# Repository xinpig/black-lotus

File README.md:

# black-lotus
Split ortholinear keyboard

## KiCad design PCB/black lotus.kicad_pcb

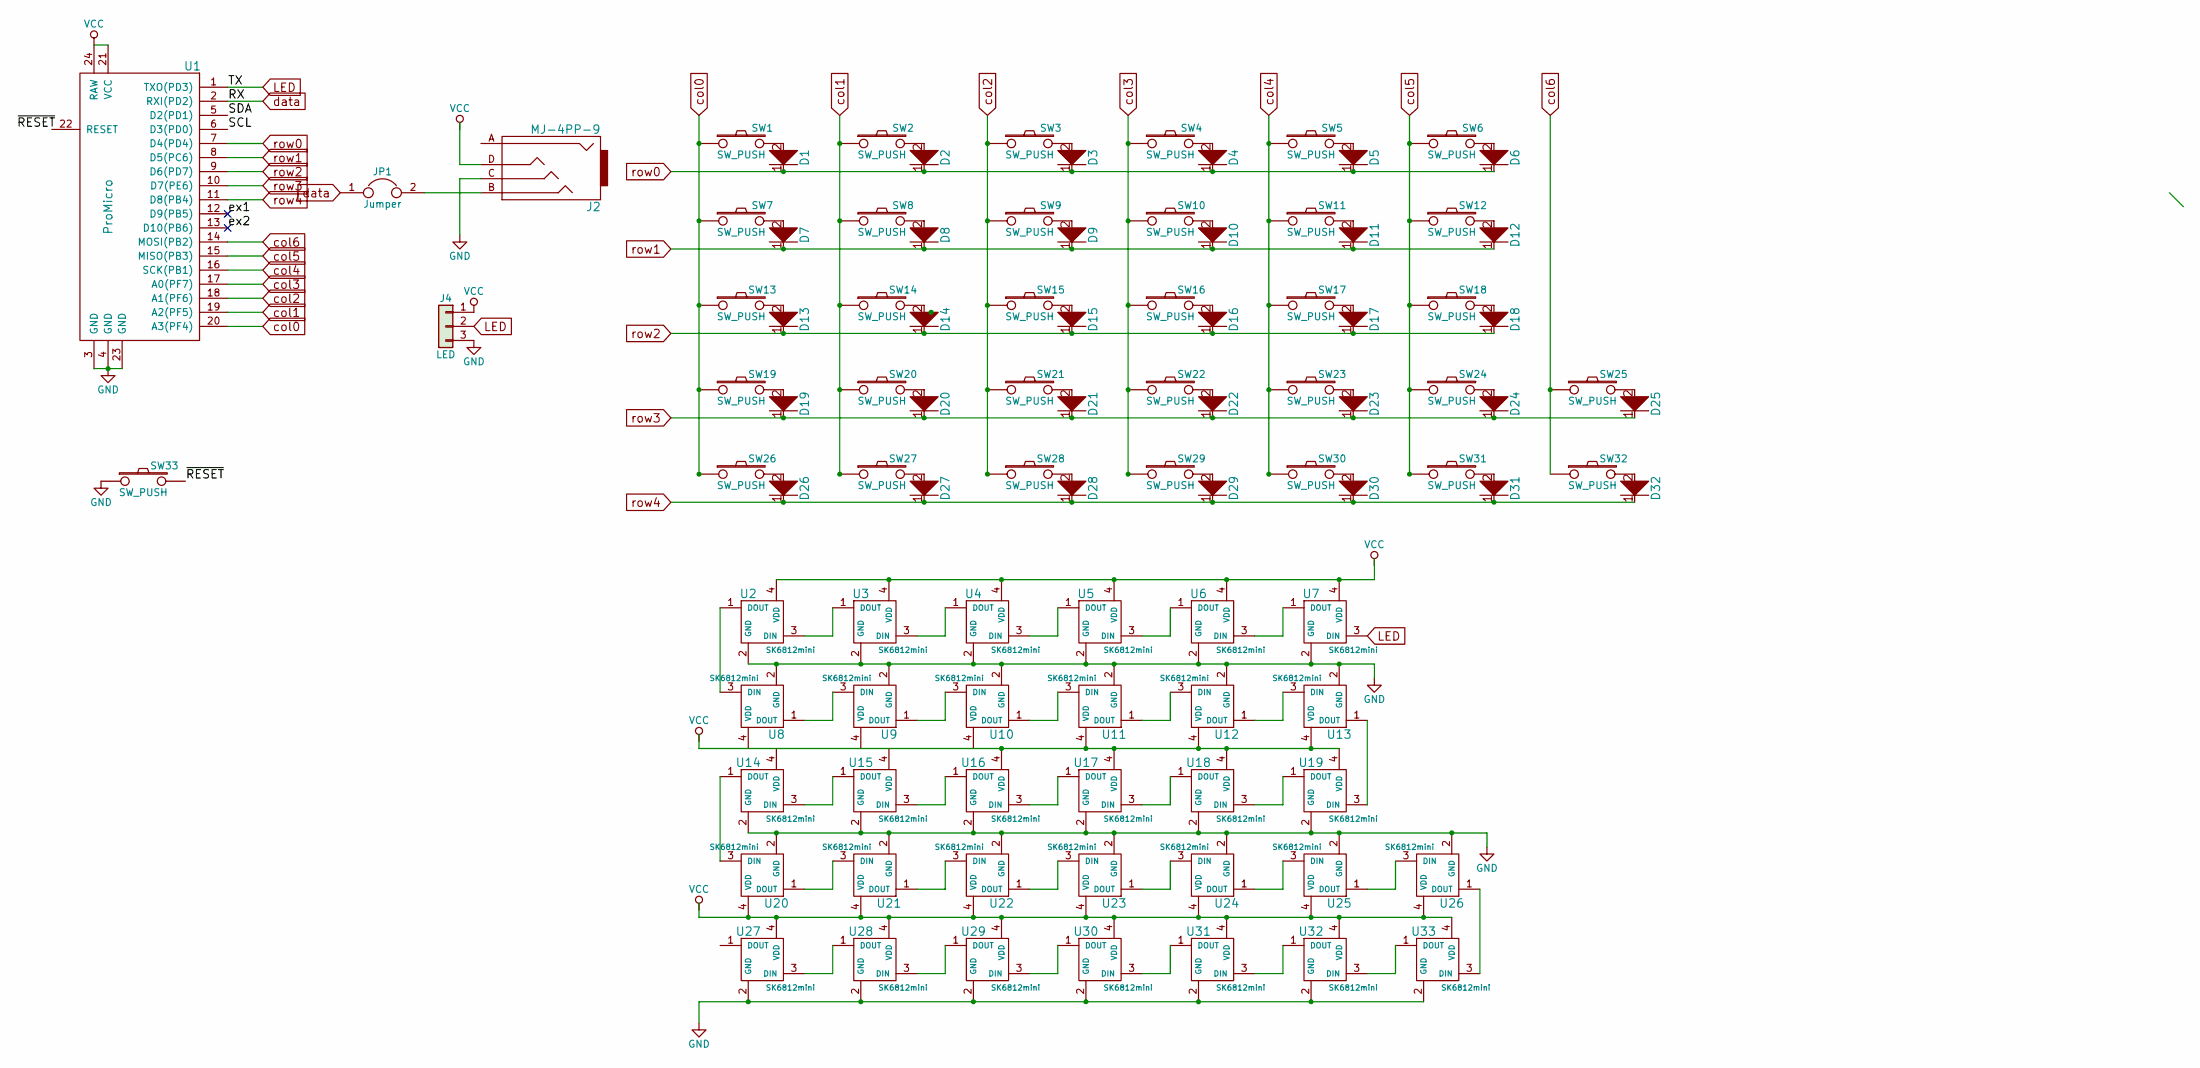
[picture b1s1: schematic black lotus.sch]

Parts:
D1, D2, D3, D4, D5, D6, D7, D8, D9, D10, D11, D12, D13, D14, D15, D16, D17, D18, D19, D20, D21, D22, D23, D24, D25, D26, D27, D28, D29, D30, D31, D32: D; D3_TH_SMD
J2: MJ-4PP-9; MJ-4PP-9_rev2
J4: LED; StripLED_rev
JP1: Jumper; JPC2
SW1, SW2, SW3, SW4, SW5, SW6, SW7, SW8, SW9, SW10, SW11, SW12, SW13, SW14, SW15, SW16, SW17, SW18, SW19, SW20, SW21, SW22, SW23, SW24, SW25, SW26, SW27, SW28, SW29, SW30, SW31, SW32: SW_PUSH; Kailh_MX_Socket_reversible
SW33: SW_PUSH; SW_3.5x6.0_TH
U1: ProMicro; ProMicro_rev
U2, U3, U4, U5, U6, U7, U8, U9, U10, U11, U12, U13, U14, U15, U16, U17, U18, U19, U20, U21, U22, U23, U24, U25, U26, U27, U28, U29, U30, U31, U32, U33: SK6812mini; SK6812MINI_rev

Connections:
/SCL: U1.6 (D3(PD0)); also elsewhere on the board
/SDA: U1.5 (D2(PD1)); also elsewhere on the board
/ex1: U1.12 (D9(PB5)); also elsewhere on the board
/ex2: U1.13 (D10(PB6)); also elsewhere on the board
/~RESET: SW33.2, U1.22 (RESET); also elsewhere on the board
GND: J2.C, J4.3, SW33.1, U1.3 (GND), U1.4 (GND), U1.23 (GND), U2.2 (GND), U3.2 (GND), U4.2 (GND), U5.2 (GND), U6.2 (GND), U7.2 (GND), U8.2 (GND), U9.2 (GND), U10.2 (GND), U11.2 (GND), U12.2 (GND), U13.2 (GND), U14.2 (GND), U15.2 (GND), U16.2 (GND), U17.2 (GND), U18.2 (GND), U19.2 (GND), U20.2 (GND), U21.2 (GND), U22.2 (GND), U23.2 (GND), U24.2 (GND), U25.2 (GND), U26.2 (GND), U27.2 (GND), U28.2 (GND), U29.2 (GND), U30.2 (GND), U31.2 (GND), U32.2 (GND), U33.2 (GND); also elsewhere on the board
LED: J4.2, U1.1 (TXO(PD3)), U7.3 (DIN); also elsewhere on the board
unnamed: D1.2, SW1.2
unnamed: D2.2, SW2.2
unnamed: D3.2, SW3.2
unnamed: D4.2, SW4.2
unnamed: D5.2, SW5.2
unnamed: D6.2, SW6.2
unnamed: D7.2, SW7.2
unnamed: D8.2, SW8.2
unnamed: D9.2, SW9.2
unnamed: D10.2, SW10.2
unnamed: D11.2, SW11.2
unnamed: D12.2, SW12.2
unnamed: D13.2, SW13.2
unnamed: D14.2, SW14.2
unnamed: D15.2, SW15.2
unnamed: D16.2, SW16.2
unnamed: D17.2, SW17.2
unnamed: D18.2, SW18.2
unnamed: D19.2, SW19.2
unnamed: D20.2, SW20.2
unnamed: D21.2, SW21.2
unnamed: D22.2, SW22.2
unnamed: D23.2, SW23.2
unnamed: D24.2, SW24.2
unnamed: D25.2, SW25.2
unnamed: D26.2, SW26.2
unnamed: D27.2, SW27.2
unnamed: D28.2, SW28.2
unnamed: D29.2, SW29.2
unnamed: D30.2, SW30.2
unnamed: D31.2, SW31.2
unnamed: D32.2, SW32.2
unnamed: J2.B, JP1.2
unnamed: U2.1 (DOUT), U8.3 (DIN)
unnamed: U2.3 (DIN), U3.1 (DOUT)
unnamed: U3.3 (DIN), U4.1 (DOUT)
unnamed: U4.3 (DIN), U5.1 (DOUT)
unnamed: U5.3 (DIN), U6.1 (DOUT)
unnamed: U6.3 (DIN), U7.1 (DOUT)
unnamed: U8.1 (DOUT), U9.3 (DIN)
unnamed: U10.1 (DOUT), U11.3 (DIN)
unnamed: U9.1 (DOUT), U10.3 (DIN)
unnamed: U11.1 (DOUT), U12.3 (DIN)
unnamed: U12.1 (DOUT), U13.3 (DIN)
unnamed: U13.1 (DOUT), U19.3 (DIN)
unnamed: U14.1 (DOUT), U20.3 (DIN)
unnamed: U14.3 (DIN), U15.1 (DOUT)
unnamed: U15.3 (DIN), U16.1 (DOUT)
unnamed: U16.3 (DIN), U17.1 (DOUT)
unnamed: U17.3 (DIN), U18.1 (DOUT)
unnamed: U18.3 (DIN), U19.1 (DOUT)
unnamed: U20.1 (DOUT), U21.3 (DIN)
unnamed: U21.1 (DOUT), U22.3 (DIN)
unnamed: U22.1 (DOUT), U23.3 (DIN)
unnamed: U23.1 (DOUT), U24.3 (DIN)
unnamed: U24.1 (DOUT), U25.3 (DIN)
unnamed: U25.1 (DOUT), U26.3 (DIN)
unnamed: U26.1 (DOUT), U33.3 (DIN)
unnamed: U27.3 (DIN), U28.1 (DOUT)
unnamed: U28.3 (DIN), U29.1 (DOUT)
unnamed: U29.3 (DIN), U30.1 (DOUT)
unnamed: U30.3 (DIN), U31.1 (DOUT)
unnamed: U31.3 (DIN), U32.1 (DOUT)
unnamed: U32.3 (DIN), U33.1 (DOUT)
VCC: J2.D, J4.1, U1.21 (VCC), U1.24 (RAW), U2.4 (VDD), U3.4 (VDD), U4.4 (VDD), U5.4 (VDD), U6.4 (VDD), U7.4 (VDD), U8.4 (VDD), U9.4 (VDD), U10.4 (VDD), U11.4 (VDD), U12.4 (VDD), U13.4 (VDD), U14.4 (VDD), U15.4 (VDD), U16.4 (VDD), U17.4 (VDD), U18.4 (VDD), U19.4 (VDD), U20.4 (VDD), U21.4 (VDD), U22.4 (VDD), U23.4 (VDD), U24.4 (VDD), U25.4 (VDD), U26.4 (VDD), U27.4 (VDD), U28.4 (VDD), U29.4 (VDD), U30.4 (VDD), U31.4 (VDD), U32.4 (VDD), U33.4 (VDD); also elsewhere on the board
col0: SW1.1, SW7.1, SW13.1, SW19.1, SW26.1, U1.20 (A3(PF4)); also elsewhere on the board
col1: SW2.1, SW8.1, SW14.1, SW20.1, SW27.1, U1.19 (A2(PF5)); also elsewhere on the board
col2: SW3.1, SW9.1, SW15.1, SW21.1, SW28.1, U1.18 (A1(PF6)); also elsewhere on the board
col3: SW4.1, SW10.1, SW16.1, SW22.1, SW29.1, U1.17 (A0(PF7)); also elsewhere on the board
col4: SW5.1, SW11.1, SW17.1, SW23.1, SW30.1, U1.16 (SCK(PB1)); also elsewhere on the board
col5: SW6.1, SW12.1, SW18.1, SW24.1, SW31.1, U1.15 (MISO(PB3)); also elsewhere on the board
col6: SW25.1, SW32.1, U1.14 (MOSI(PB2)); also elsewhere on the board
data: JP1.1, U1.2 (RXI(PD2)); also elsewhere on the board
row0: D1.1, D2.1, D3.1, D4.1, D5.1, D6.1, U1.7 (D4(PD4)); also elsewhere on the board
row1: D7.1, D8.1, D9.1, D10.1, D11.1, D12.1, U1.8 (D5(PC6)); also elsewhere on the board
row2: D13.1, D14.1, D15.1, D16.1, D17.1, D18.1, U1.9 (D6(PD7)); also elsewhere on the board
row3: D19.1, D20.1, D21.1, D22.1, D23.1, D24.1, D25.1, U1.10 (D7(PE6)); also elsewhere on the board
row4: D26.1, D27.1, D28.1, D29.1, D30.1, D31.1, D32.1, U1.11 (D8(PB4)); also elsewhere on the board

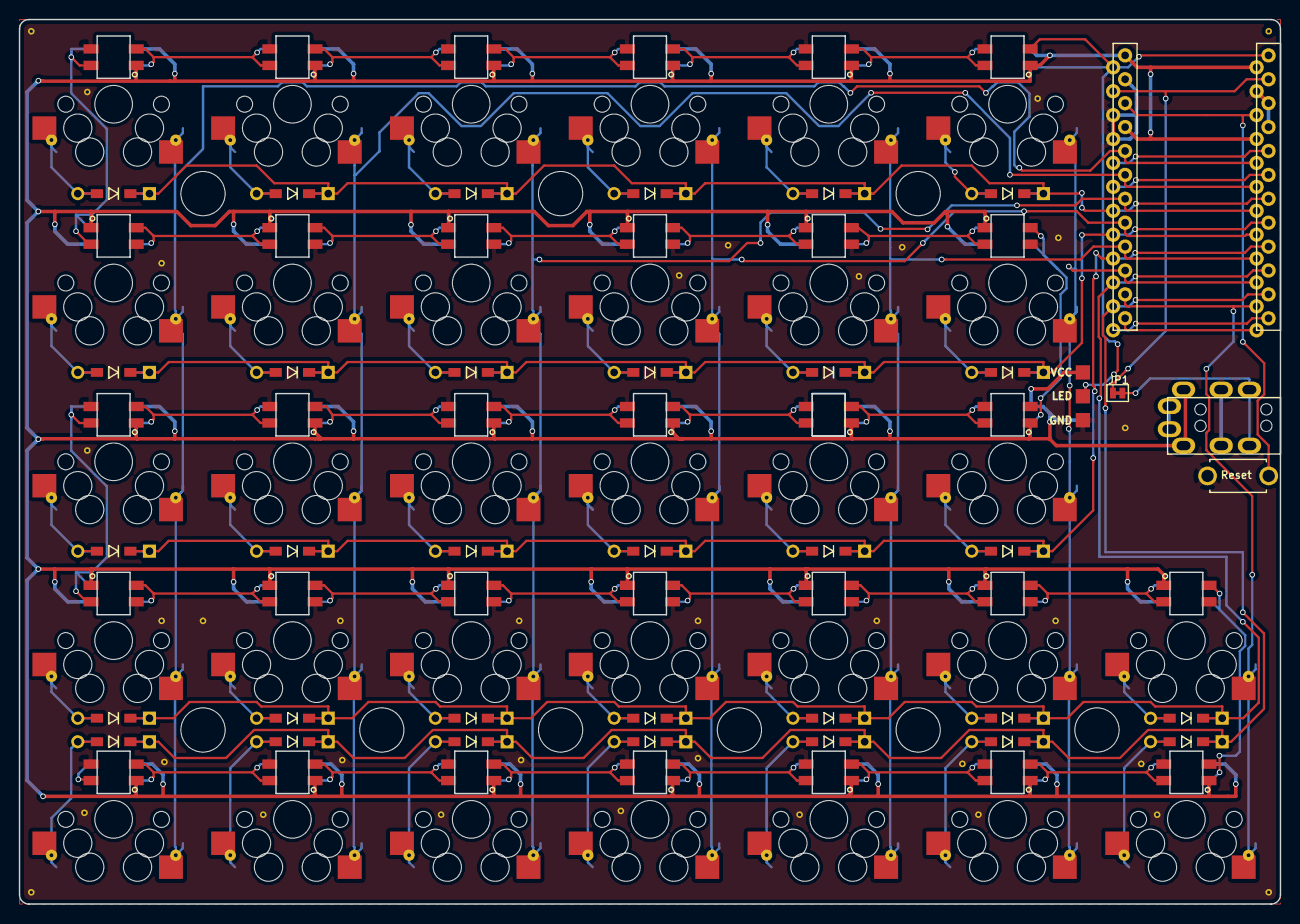
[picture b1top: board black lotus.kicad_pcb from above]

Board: 2 copper layers, 134.0 x 94.0 mm, 111 parts (1 on the bottom side), 85 nets.

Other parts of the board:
HOLE_3M1, HOLE_3M2, HOLE_3M3, HOLE_3M4, HOLE_3M5, HOLE_3M6, HOLE_3M7, HOLE_3M8, HOLE_3M9: VAL**; HOLE_M2_TH
U34: ProMicro; ProMicro_rev

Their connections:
/SCL: U34.6; also elsewhere on the board
/SDA: U34.5; also elsewhere on the board
/ex1: U34.12; also elsewhere on the board
/ex2: U34.13; also elsewhere on the board
/~RESET: U34.22; also elsewhere on the board
GND: U34.3, U34.4, U34.23; also elsewhere on the board
LED: U34.1; also elsewhere on the board
VCC: U34.21, U34.24; also elsewhere on the board
col0: U34.20; also elsewhere on the board
col1: U34.19; also elsewhere on the board
col2: U34.18; also elsewhere on the board
col3: U34.17; also elsewhere on the board
col4: U34.16; also elsewhere on the board
col5: U34.15; also elsewhere on the board
col6: U34.14; also elsewhere on the board
data: U34.2; also elsewhere on the board
row0: U34.7; also elsewhere on the board
row1: U34.8; also elsewhere on the board
row2: U34.9; also elsewhere on the board
row3: U34.10; also elsewhere on the board
row4: U34.11; also elsewhere on the board

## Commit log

2018-06-06 Add files via upload
    Updated silkscreen, GND layers
